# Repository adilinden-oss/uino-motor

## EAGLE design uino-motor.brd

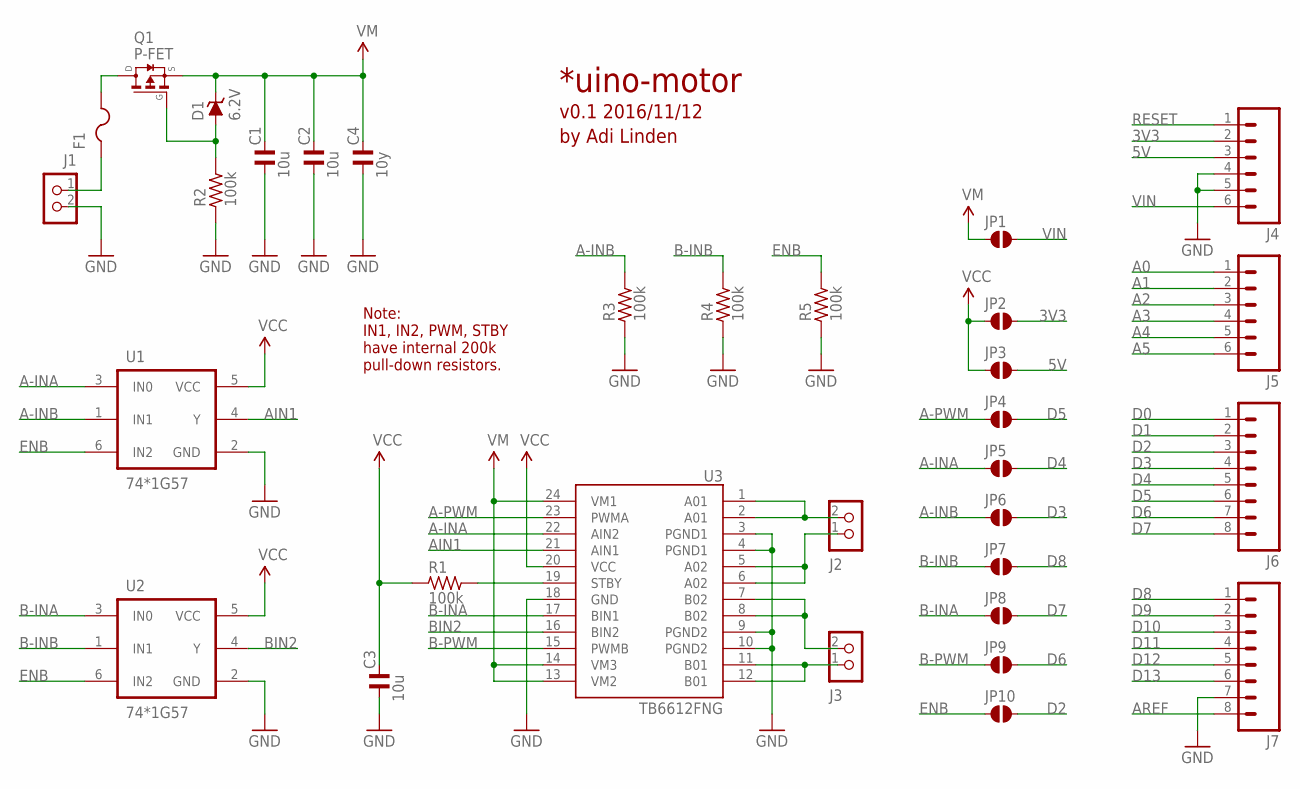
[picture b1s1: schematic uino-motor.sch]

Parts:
C1, C2, C3: 10u; C0805MP
C4: 10y; C0805MP
D1: 6.2V; SOD323
F1: FUSE_PTC-TH; PTC
J1, J2, J3: CON_TERMINAL_BLOCK_02-5MM; TERMINAL_BLOCK_2P_5
J4, J5: M06SIP; 1X06
J6, J7: M081X08; 1X08
JP1, JP2, JP3, JP4, JP5, JP6, JP7, JP8, JP9, JP10: SJ-035
Q1: P-FET; SOT23
R1, R2, R3, R4, R5: 100k; R0805MP
U1, U2: 74*1G57; SOT23-6
U3: TB6612FNG; SSOP24

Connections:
3V3: J4.2, JP2.2
5V: J4.3, JP3.2
A0: J5.1
A1: J5.2
A01: J2.2, U3.1 (A01), U3.2 (A01)
A2: J5.3
A02: J2.1, U3.5 (A02), U3.6 (A02)
A3: J5.4
A4: J5.5
A5: J5.6
A-INA: JP5.1, U1.3 (IN0), U3.22 (AIN2)
A-INB: JP6.1, R3.2, U1.1 (IN1)
A-PWM: JP4.1, U3.23 (PWMA)
AIN1: U1.4 (Y), U3.21 (AIN1)
AREF: J7.8
B01: J3.1, U3.11 (B01), U3.12 (B01)
B02: J3.2, U3.7 (B02), U3.8 (B02)
B-INA: JP8.1, U2.3 (IN0), U3.17 (BIN1)
B-INB: JP7.1, R4.2, U2.1 (IN1)
B-PWM: JP9.1, U3.15 (PWMB)
BIN2: U2.4 (Y), U3.16 (BIN2)
D0: J6.1
D1: J6.2
D2: J6.3, JP10.2
D3: J6.4, JP6.2
D4: J6.5, JP5.2
D5: J6.6, JP4.2
D6: J6.7, JP9.2
D7: J6.8, JP8.2
D8: J7.1, JP7.2
D9: J7.2
D10: J7.3
D11: J7.4
D12: J7.5
D13: J7.6
ENB: JP10.1, R5.2, U1.6 (IN2), U2.6 (IN2)
GND: C1.1, C2.1, C3.1, C4.1, J1.2, J4.4, J4.5, J7.7, R2.1, R3.1, R4.1, R5.1, U1.2 (GND), U2.2 (GND), U3.3 (PGND1), U3.4 (PGND1), U3.9 (PGND2), U3.10 (PGND2), U3.18 (GND)
unnamed: R1.2, U3.19 (STBY)
unnamed: F1.P$1 (1), J1.1
unnamed: D1.A, Q1.1 (G), R2.2
unnamed: F1.P$2 (2), Q1.3 (D)
RESET: J4.1
VCC: C3.2, JP2.1, JP3.1, R1.1, U1.5 (VCC), U2.5 (VCC), U3.20 (VCC)
VDD: C1.2, C2.2, C4.2, D1.C, JP1.1, Q1.2 (S), U3.13 (VM2), U3.14 (VM3), U3.24 (VM1)
VIN: J4.6, JP1.2

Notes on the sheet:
Note: IN1, IN2, PWM, STBY have internal 200k pull-down resistors.
*uino-motor
v0.1 2016/11/12
by Adi Linden

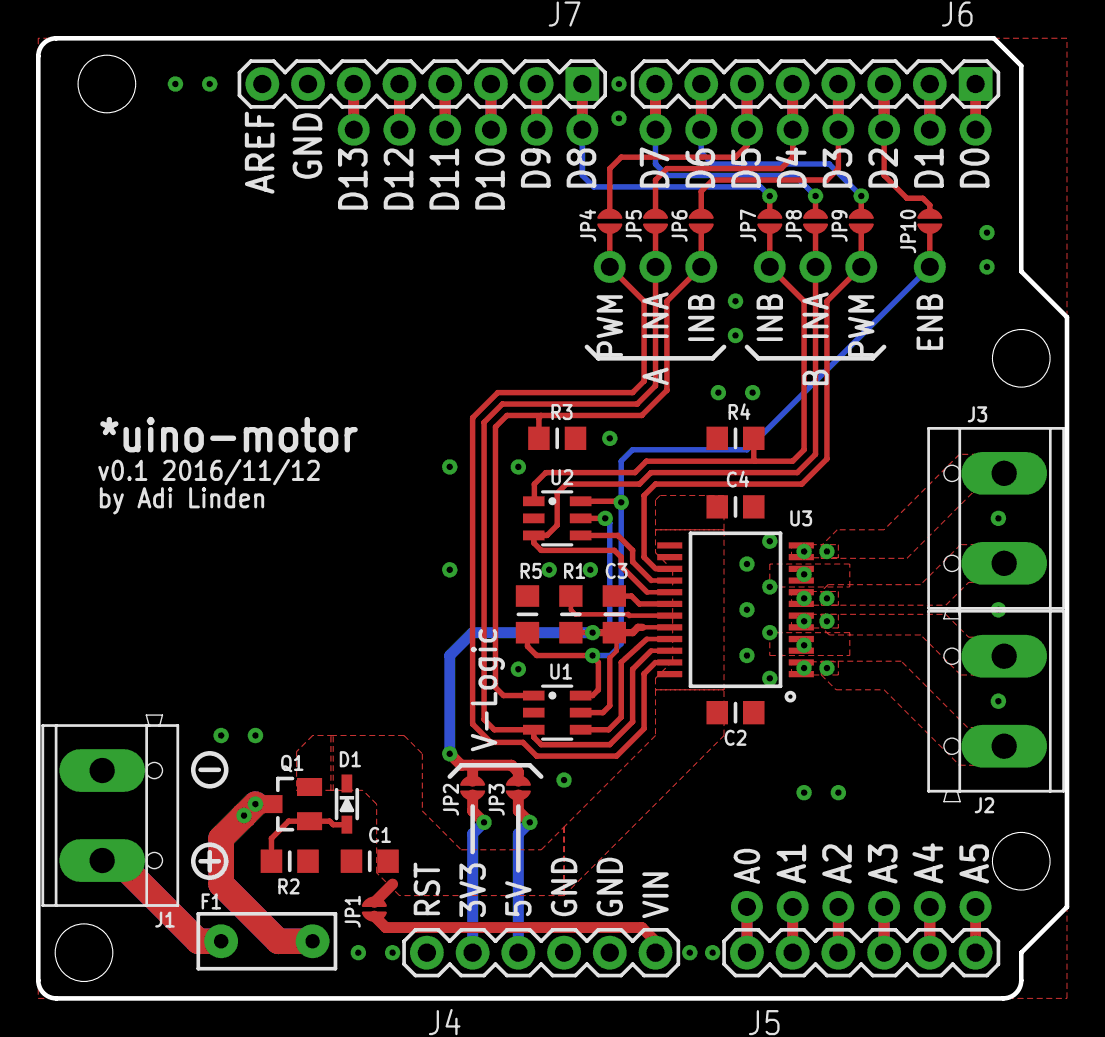
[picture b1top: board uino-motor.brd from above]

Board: 2 copper layers, 57.1 x 53.3 mm, 32 parts (0 on the bottom side), 30 nets.

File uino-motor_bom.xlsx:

Parts | Qty | Value | Manufacturer Part Number | DigiKey Part Number | Package | Description
C1, C2, C3,C4 | 3 | 10u | CL21A106KOQNNNG | 1276-6455-1-ND | C0805 | 10µF ±10% 16V Ceramic Capacitor X5R 0805 (2012 Metric)
D1 | 1 | 6.2V Zener | DZ2J062M0L | DZ2J062M0LCT-ND | SOD323 | Zener Diode 6.2V 200mW ±5% Surface Mount SMini2-F5-B
F1 | 1 |  | 0ZRA0300FF1C | 507-1304-ND | 5mm | PTC Resettable Fuse 16V 3A Ih Through Hole Radial, Disc
J1, J2, J3 | 3 | Terminal | OSTTC022162 | ED2609-ND | 7.6x10.16mm | 2 Position Wire to Board Terminal Block Horizontal with Board 0.200" (5.08mm) T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
J4, J5 | 2 | Header 1x6 | PPTC061LFBN-RC | S7004-ND | 1X06 | 6 Position Header Connector 0.100" (2.54mm) Through Hole Tin
J6, J7 | 2 | Header 1x8 | PPTC081LFBN-RC | S7006-ND | 1X08 | 8 Position Header Connector 0.100" (2.54mm) Through Hole Tin
Q1 | 1 | P-FET | SSM3J328R,LF | SSM3J328RLFCT-ND | SOT23 | MOSFET P-CH 20V 6A SOT23F
R1, R2, R3, R4, R5 | 5 | 100k | RC0805JR-07100KL | 311-100KARCT-ND | R0805 | RES SMD 100K OHM 5% 1/8W 0805
U1, U2 | 2 | 74*1G57 | 74LVC1G57W6-7 | 74LVC1G57W6-7CT-ND | SOT23-6 | Configurable Multiple Function Configurable 1 Circuit 3 Input SOT-26
U3 | 1 | TB6612FNG | TB6612FNG,C,8,EL | TB6612FNGC8ELCT-ND | SSOP24 | Motor Driver Power MOSFET Parallel 24-SSOP

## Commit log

2016-11-10 Added uino-motor.
2016-11-11 Added pull-down at logic gate inputs. Routed board.
2016-11-12 Parts placed and major routing completed.
2016-11-13 Added values. Version 0.1
2016-11-14 Added BOM.
2016-11-17 Included *Dcou layers in png.
2016-11-17 Created gerber for FusionPCB order.

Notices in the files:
parts and their libraries:
74LV: Copyright (C) 2008, Bob Starr
rc-master-smd: Copyright (C) 2007-2008, Bob Starr
jumpers: Copyright (C) 2009, Bob Starr
SparkFun-PowerIC: Licensing: Creative Commons ShareAlike 4.0 International - https://creativecommons.org/licenses/by-sa/4.0
